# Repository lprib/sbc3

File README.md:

# sbc3: small computing environment
Self contained board that can be easily programmed on target for fun little
games or GUIs. Inspired by the environment presented by TI calculators and
TI-BASIC.

# Directory structure
```
sbc3
|_ art: various images for putting on PCB and for on-screen graphics
|_ cubemx: STM32 CubeMX projects for pinmapping
|_ docs: datasheets etc
|  |_ cpu_hardware: hardware support and layout for STM32s
|  |_ hardware: various datasheets for parts used
|  \_ sofware: CPU ref manuals etc
|_ img: images for docs
|_ keyboard_v1: kicad project for keyboard
|_ main_board_v1: kicad project for main board
|_ rust_firmware: Firmware and screen driver in Rust (abandoned for now)
\_ software: (mostly c++) software and firmware
   |_ cmake: cmake scripts
   |_ firmware: firmware for main_board_v1
   |  |_ app: main application sources
   |  \_ (other dirs): supporting libraries unchanged from CubeMX/FreeRTOS upstream
   \_ vm: virtual machine
      |_ analysis: jupyter notebook for vm stat calculations
      |_ engine: main vm sources (portable)
      |_ pc_port: raylib port of VM for desktop
      |_ programs: sbc3 assembly programs
      |_ tests: vm unit tests (lol)
      |_ vscode-extension-sbcs-syntax: syntax support in VSCode for SBC3 assembly
      \_ as2.py: sbc3 vm bytecode assembler
```

## Components
### main_board_v1
#### System diagram

#### PCB

#### Manufactured

- PCB and assembly done by JLCPCB
- Extended parts used:
  - TLV320DAC3101IRHBR Audio DAC
  - 475900001 Micro-USB connector
  - LD1117S33TR 3V3 Linear Regulator
    - Honestly can't remember why I went for this one instead of the JLC
    preferred part AMS1117-3.3. Maybe max current
  - LD1117S18TR 1V8 Linear Regulator (for DAC)
  - STM32F405VGT6 MCU

#### Changes and ideas for v2
- [ ] Ability to disconnect 3v3 from rs485 connectors
- [ ] Isolation transformers on rs485 for long connections
- [ ] External flash or eeprom or FRAM for filesystem
- [ ] "Cartridges" with flash
- [ ] Label all the headers pin for pin to avoid looking on the schematic every
time you're connecting the SWD
- [ ] Fix BOOT0/BOOT1? Or just 0ohm unpopulated for de-bricking?
- [ ] Proper enclosure
- [ ] ESD diode protection on all inputs
- [ ] External qspi flash (w25q128jv)
- [ ] Wire OE on LED shift registers to a PWMable pin! So you can easily pwm the brightness
- [ ] 18650 batteries + holder?
- [ ] smaller form factor with parts hidden underscreen and less rs485 or more
compact layout (look for resistor/cap sizing for 0402 wattage)
- [ ] ACTUALLY WIRE UP THE BUTTONS AND ENCODER THIS TIME!
    - Of all the things to screw up on the first PCB run, I didn't expect to
    completely forget to connect the button and rotary nets
- [ ] Tiny JST connectors really are shit! Hot pluggable trs circuit?
Enable/disabable power chip? Need to get this right before making a bunch of peripheral boards.

### keyboard_v1
#### System diagram

#### PCB

Not yet manufactured, since still thinking about re-doing the comms (definitely
not going to use the current JST connectors as theyre much too finicky).

### virtual machine
Also included is a stack based virtual bytecode machine (see [software/vm](./software/vm)).
The bytecode can call out to pre-defined system modules, including graphics
routines. Below is an example of the main board STM32 and a Linux desktop
running the same bytecode program.

#### STM32

#### Linux desktop

As the bytecode is stack based, a thin forth layer has been built for it, which
is currently assembled by a python script. See the source program for the above gifs [here](./software/vm/programs/tilemap.sbcs).

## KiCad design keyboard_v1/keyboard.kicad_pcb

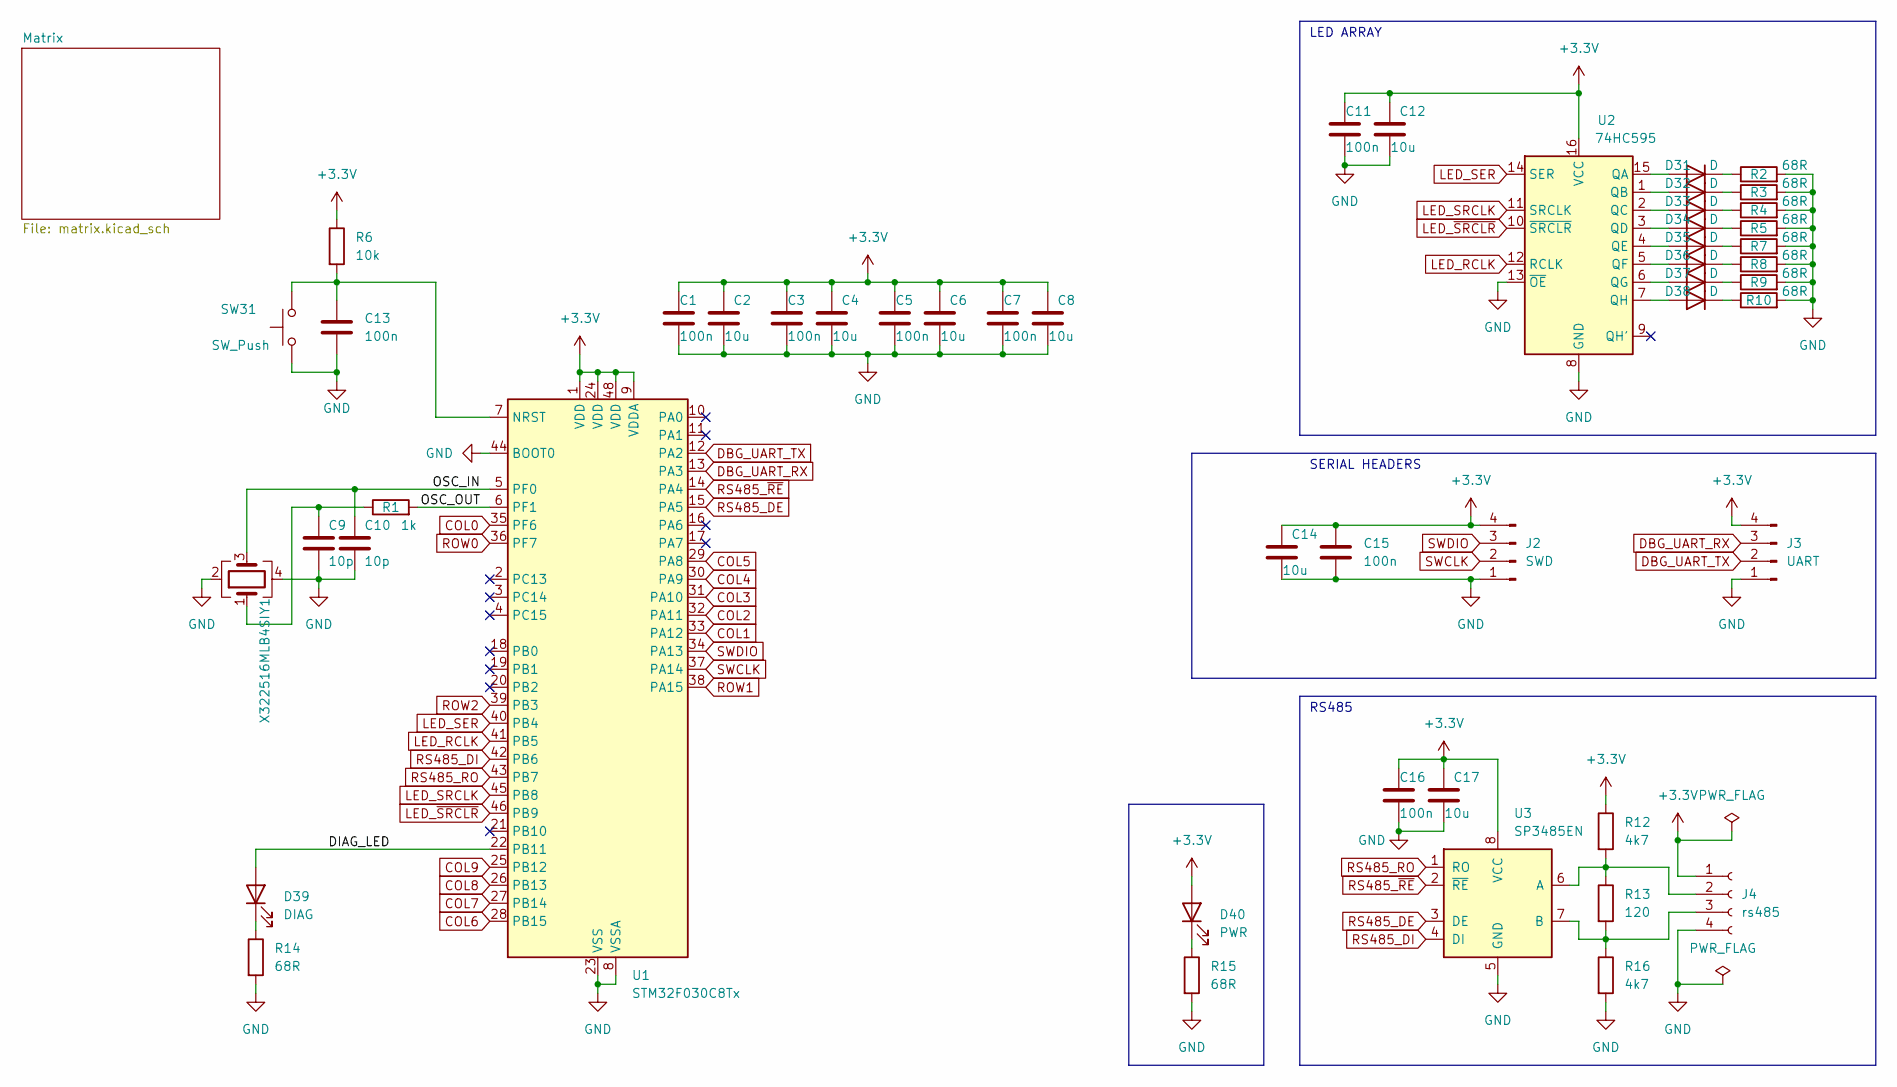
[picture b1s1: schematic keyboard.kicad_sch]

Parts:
C1, C3, C5, C7, C11, C13, C15, C16: 100n; C_0402_1005Metric; LCSC C307331
C2, C4, C6, C8, C12, C14, C17: 10u; C_0603_1608Metric; LCSC C96446
C9, C10: 10p; C_0402_1005Metric; LCSC C32949
D31, D32, D33, D34, D35, D36, D37, D38: D; D_0603_1608Metric; LCSC C72038
D39: DIAG; D_0603_1608Metric; LCSC C72038
D40: PWR; D_0603_1608Metric; LCSC C72038
J2: SWD; PinHeader_1x04_P2.54mm_Vertical
J3: UART; PinHeader_1x04_P2.54mm_Vertical
J4: rs485; JST_SH_SM04B-SRSS-TB_1x04-1MP_P1.00mm_Horizontal
R1: 1k; R_0402_1005Metric; LCSC C11702
R2, R3, R4, R5, R7, R8, R9, R10, R14, R15: 68R; R_0603_1608Metric; LCSC C27592
R6: 10k; R_0402_1005Metric; LCSC C25744
R12, R16: 4k7; R_1206_3216Metric; LCSC C17936
R13: 120; R_1206_3216Metric; LCSC C17909
SW31: SW_Push; SW_Push_1P1T_XKB_TS-1187A; LCSC C318884
U1: STM32F030C8Tx; LQFP-48_7x7mm_P0.5mm; LCSC C23922
U2: 74HC595; SOIC-16_3.9x9.9mm_P1.27mm; LCSC C5947
U3: SP3485EN; SOIC-8_3.9x4.9mm_P1.27mm
Y1: X322516MLB4SI; Crystal_SMD_SeikoEpson_TSX3225-4Pin_3.2x2.5mm; LCSC C13738

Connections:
+3.3V: C1.1, C2.1, C3.1, C4.1, C5.1, C6.1, C7.1, C8.1, C11.1, C12.1, C14.1, C15.1, C16.1, C17.1, D40.2 (A), J2.4, J3.4, J4.1, R6.1, R12.1, U1.1 (VDD), U1.9 (VDDA), U1.24 (VDD), U1.48 (VDD), U2.16 (VCC), U3.8 (VCC)
/DIAG_LED: D39.2 (A), U1.22 (PB11)
/OSC_IN: C10.1, U1.5 (PF0), Y1.3
/OSC_OUT: R1.2, U1.6 (PF1)
COL0: U1.35 (PF6); also elsewhere on the board
COL1: U1.33 (PA12); also elsewhere on the board
COL2: U1.32 (PA11); also elsewhere on the board
COL3: U1.31 (PA10); also elsewhere on the board
COL4: U1.30 (PA9); also elsewhere on the board
COL5: U1.29 (PA8); also elsewhere on the board
COL6: U1.28 (PB15); also elsewhere on the board
COL7: U1.27 (PB14); also elsewhere on the board
COL8: U1.26 (PB13); also elsewhere on the board
COL9: U1.25 (PB12); also elsewhere on the board
DBG_UART_RX: J3.3, U1.13 (PA3)
DBG_UART_TX: J3.2, U1.12 (PA2)
GND: C1.2, C2.2, C3.2, C4.2, C5.2, C6.2, C7.2, C8.2, C9.2, C10.2, C11.2, C12.2, C13.2, C14.2, C15.2, C16.2, C17.2, J2.1, J3.1, J4.4, R2.2, R3.2, R4.2, R5.2, R7.2, R8.2, R9.2, R10.2, R14.2, R15.2, R16.2, SW31.1, U1.8 (VSSA), U1.23 (VSS), U1.44 (BOOT0), U1.47 (VSS), U2.8 (GND), U2.13 (~OE), U3.5 (GND), Y1.2, Y1.4
LED_RCLK: U1.41 (PB5), U2.12 (RCLK)
LED_SER: U1.40 (PB4), U2.14 (SER)
LED_SRCLK: U1.45 (PB8), U2.11 (SRCLK)
LED_~SRCLR: U1.46 (PB9), U2.10 (~SRCLR)
unnamed: C9.1, R1.1, Y1.1
unnamed: D31.2 (A), U2.15 (QA)
unnamed: D31.1 (K), R2.1
unnamed: D32.2 (A), U2.1 (QB)
unnamed: D32.1 (K), R3.1
unnamed: D33.2 (A), U2.2 (QC)
unnamed: D33.1 (K), R4.1
unnamed: D34.2 (A), U2.3 (QD)
unnamed: D34.1 (K), R5.1
unnamed: D35.2 (A), U2.4 (QE)
unnamed: D35.1 (K), R7.1
unnamed: D36.2 (A), U2.5 (QF)
unnamed: D36.1 (K), R8.1
unnamed: D37.2 (A), U2.6 (QG)
unnamed: D37.1 (K), R9.1
unnamed: D38.2 (A), U2.7 (QH)
unnamed: D38.1 (K), R10.1
unnamed: D39.1 (K), R14.1
unnamed: D40.1 (K), R15.1
unnamed: J4.2, R12.2, R13.1, U3.6 (A)
unnamed: J4.3, R13.2, R16.1, U3.7 (B)
unnamed: C13.1, R6.2, SW31.2, U1.7 (NRST)
ROW0: U1.36 (PF7); also elsewhere on the board
ROW1: U1.38 (PA15); also elsewhere on the board
ROW2: U1.39 (PB3); also elsewhere on the board
RS485_DE: U1.15 (PA5), U3.3 (DE)
RS485_DI: U1.42 (PB6), U3.4 (DI)
RS485_RO: U1.43 (PB7), U3.1 (RO)
RS485_~RE: U1.14 (PA4), U3.2 (~RE)
SWCLK: J2.2, U1.37 (PA14)
SWDIO: J2.3, U1.34 (PA13)

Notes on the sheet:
RS485
SERIAL HEADERS
LED ARRAY

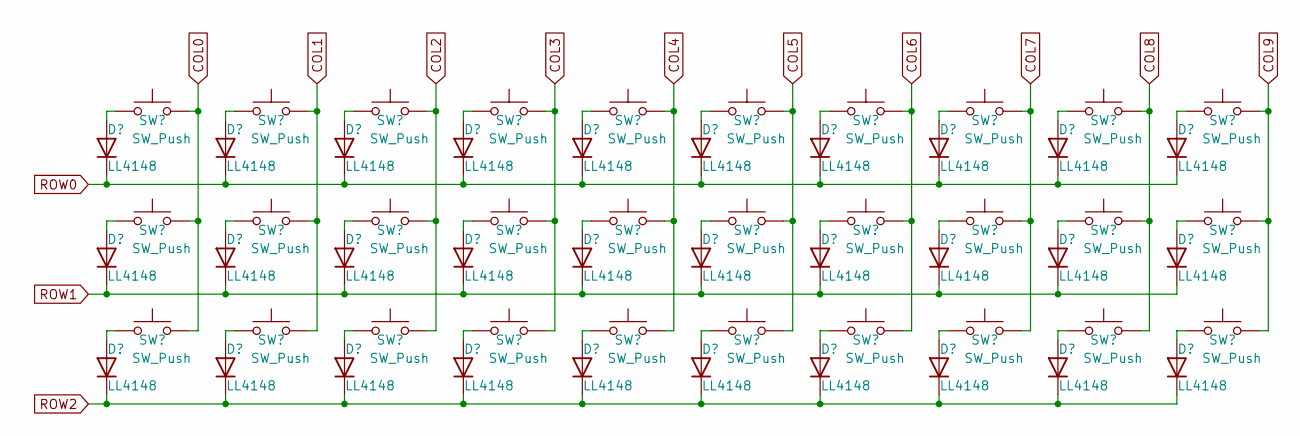
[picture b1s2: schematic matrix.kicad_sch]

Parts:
D1, D2, D3, D4, D5, D6, D7, D8, D9, D10, D11, D12, D13, D14, D15, D16, D17, D18, D19, D20, D21, D22, D23, D24, D25, D26, D27, D28, D29, D30: LL4148; D_1206_3216Metric; LCSC C9808
SW1, SW2, SW3, SW4, SW5, SW6, SW7, SW8, SW9, SW10, SW11, SW12, SW13, SW14, SW15, SW16, SW17, SW18, SW19, SW20, SW21, SW22, SW23, SW24, SW25, SW26, SW27, SW28, SW29, SW30: SW_Push; SW_Cherry_MX_1.00u_PCB

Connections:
COL0: SW1.2, SW11.2, SW21.2; also elsewhere on the board
COL1: SW2.2, SW12.2, SW22.2; also elsewhere on the board
COL2: SW3.2, SW13.2, SW23.2; also elsewhere on the board
COL3: SW4.2, SW14.2, SW24.2; also elsewhere on the board
COL4: SW5.2, SW15.2, SW25.2; also elsewhere on the board
COL5: SW6.2, SW16.2, SW26.2; also elsewhere on the board
COL6: SW7.2, SW17.2, SW27.2; also elsewhere on the board
COL7: SW8.2, SW18.2, SW28.2; also elsewhere on the board
COL8: SW9.2, SW19.2, SW29.2; also elsewhere on the board
COL9: SW10.2, SW20.2, SW30.2; also elsewhere on the board
unnamed: D1.2 (A), SW1.1
unnamed: D2.2 (A), SW2.1
unnamed: D3.2 (A), SW3.1
unnamed: D4.2 (A), SW4.1
unnamed: D5.2 (A), SW5.1
unnamed: D6.2 (A), SW6.1
unnamed: D7.2 (A), SW7.1
unnamed: D8.2 (A), SW8.1
unnamed: D9.2 (A), SW9.1
unnamed: D10.2 (A), SW10.1
unnamed: D11.2 (A), SW11.1
unnamed: D12.2 (A), SW12.1
unnamed: D13.2 (A), SW13.1
unnamed: D14.2 (A), SW14.1
unnamed: D15.2 (A), SW15.1
unnamed: D16.2 (A), SW16.1
unnamed: D17.2 (A), SW17.1
unnamed: D18.2 (A), SW18.1
unnamed: D19.2 (A), SW19.1
unnamed: D20.2 (A), SW20.1
unnamed: D21.2 (A), SW21.1
unnamed: D22.2 (A), SW22.1
unnamed: D23.2 (A), SW23.1
unnamed: D24.2 (A), SW24.1
unnamed: D25.2 (A), SW25.1
unnamed: D26.2 (A), SW26.1
unnamed: D27.2 (A), SW27.1
unnamed: D28.2 (A), SW28.1
unnamed: D29.2 (A), SW29.1
unnamed: D30.2 (A), SW30.1
ROW0: D1.1 (K), D2.1 (K), D3.1 (K), D4.1 (K), D5.1 (K), D6.1 (K), D7.1 (K), D8.1 (K), D9.1 (K), D10.1 (K); also elsewhere on the board
ROW1: D11.1 (K), D12.1 (K), D13.1 (K), D14.1 (K), D15.1 (K), D16.1 (K), D17.1 (K), D18.1 (K), D19.1 (K), D20.1 (K); also elsewhere on the board
ROW2: D21.1 (K), D22.1 (K), D23.1 (K), D24.1 (K), D25.1 (K), D26.1 (K), D27.1 (K), D28.1 (K), D29.1 (K), D30.1 (K); also elsewhere on the board

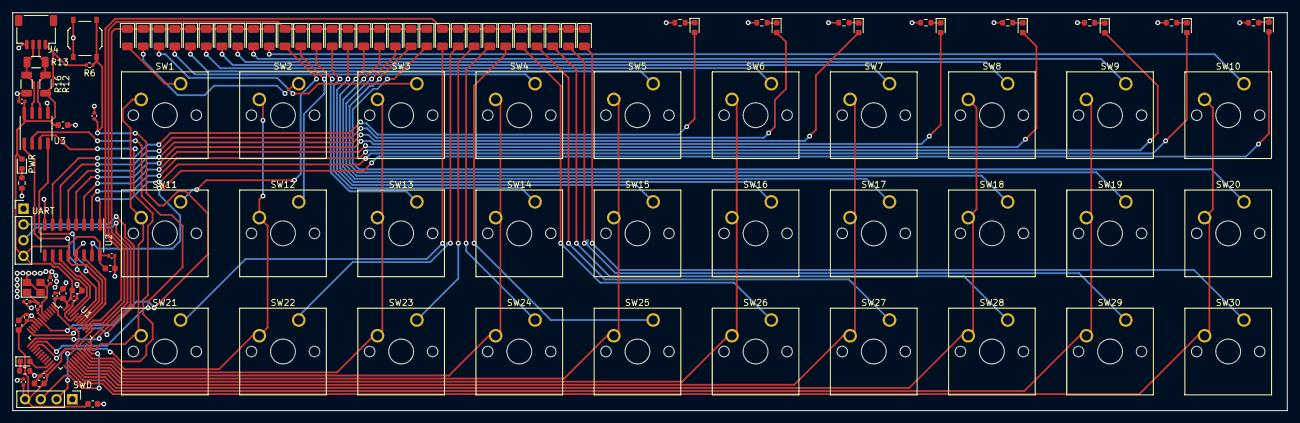
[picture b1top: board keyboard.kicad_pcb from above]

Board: 2 copper layers, 205.5 x 64.2 mm, 110 parts (0 on the bottom side), 82 nets.

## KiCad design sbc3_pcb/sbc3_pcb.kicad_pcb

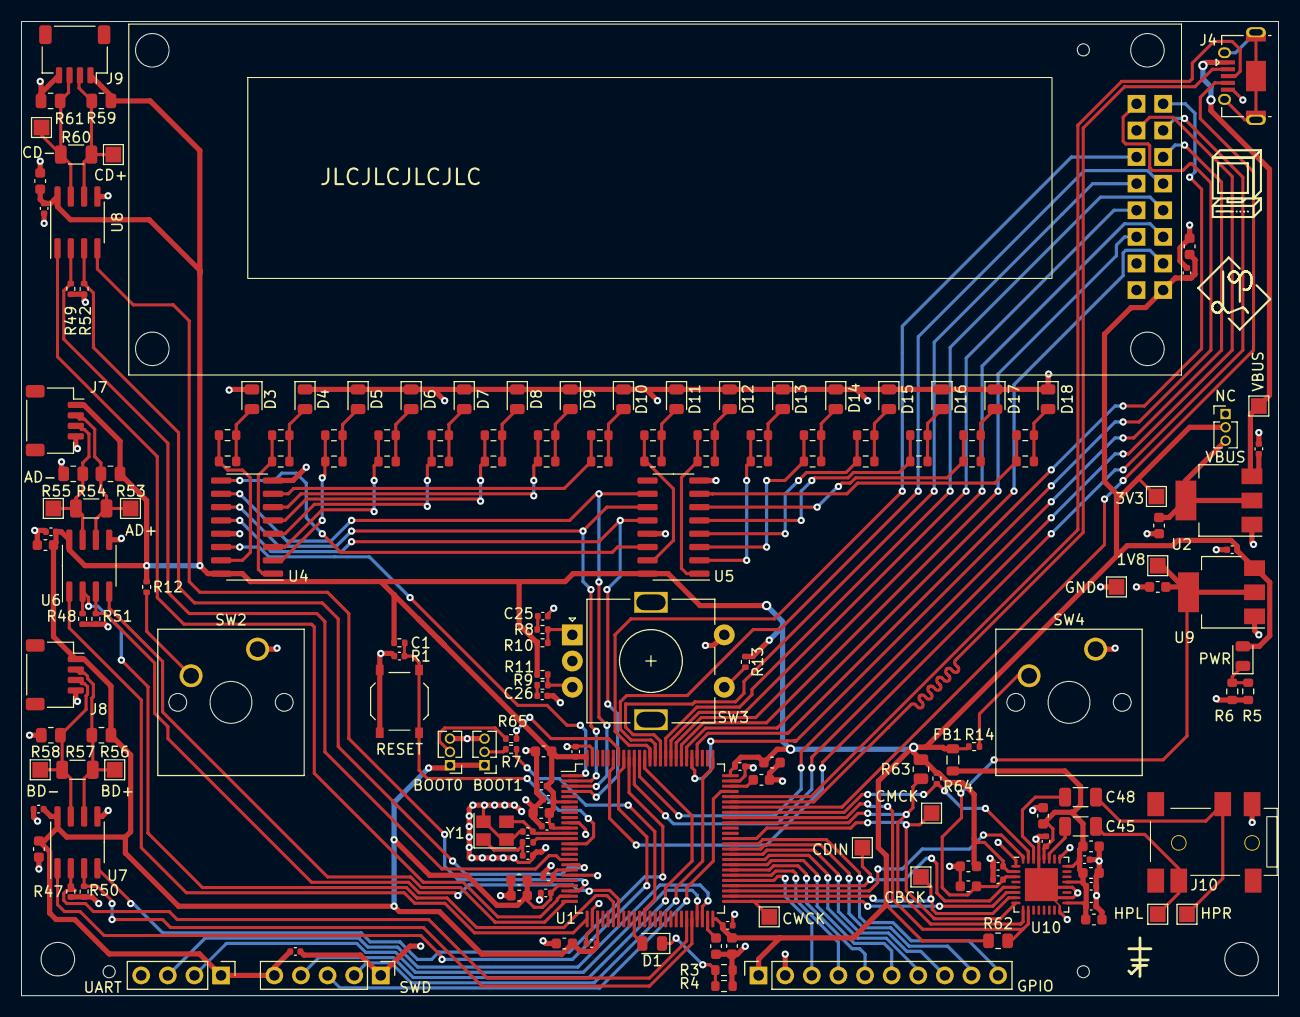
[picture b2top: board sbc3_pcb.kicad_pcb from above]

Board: 2 copper layers, 120.0 x 93.0 mm, 181 parts (0 on the bottom side), 122 nets.

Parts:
C1, C6, C9, C11, C12, C14, C17, C18, C20, C22, C24, C28, C29, C31, C33, C35, C40, C42, C44, C47, C50, C52: 100n; C_0402_1005Metric
C2, C3: 10p; C_0402_1005Metric
C4, C5: 2.2u; C_0603_1608Metric
C7: 1u; C_0402_1005Metric
C8, C10, C13, C15, C16, C19, C21, C23, C27, C30, C32, C34, C36, C39, C41, C43, C46, C49, C51: 10u; C_0603_1608Metric
C25, C26: 10n; C_0402_1005Metric
C45, C48: 47u; C_1206_3216Metric
D1: DBG; LED_0805_2012Metric
D2: PWR; LED_0805_2012Metric
D3, D4, D5, D6, D7, D8, D9, D10, D11, D12, D13, D14, D15, D16, D17, D18: LED; LED_0805_2012Metric
FB1: FerriteBead; L_0805_2012Metric
H1, H2: MountingHole; MountingHole_3.2mm_M3
H3, H4, H5: MountingHole; MountingHole_JLCPCB_Assembly
J1: VBUS CON; PinHeader_1x03_P1.27mm_Vertical
J2: BOOT0; PinHeader_1x03_P1.27mm_Vertical
J3: GPIO; PinSocket_1x10_P2.54mm_Vertical
J4: USB_B_Micro; USB_Micro-AB_Molex_47590-0001
J5: UART; PinHeader_1x04_P2.54mm_Vertical
J6: SWD; PinHeader_1x05_P2.54mm_Vertical
J7, J8, J9: Conn_01x04_Socket; JST_SH_SM04B-SRSS-TB_1x04-1MP_P1.00mm_Horizontal
J10: PJ-342
J11: BOOT1; PinHeader_1x03_P1.27mm_Vertical
R1, R7, R8, R9, R10, R11, R12, R13, R14, R47, R48, R49, R50, R51, R52, R64, R65: 10k; R_0402_1005Metric
R2: 1k; R_0402_1005Metric
R3, R4, R5, R6, R15, R16, R17, R18, R19, R20, R21, R22, R23, R24, R25, R26, R27, R28, R29, R30, R31, R32, R33, R34, R35, R36, R37, R38, R39, R40, R41, R42, R43, R44, R45, R46: 150; R_0603_1608Metric
R53, R55, R56, R58, R59, R61, R62, R63: 4k7; R_0805_2012Metric
R54, R57, R60: 120; R_1206_3216Metric
SW1: RESET; SW_Push_1P1T_XKB_TS-1187A
SW2, SW4: CHERRY_SWITCH; SW_Cherry_MX_1.00u_PCB
SW3: RotaryEncoder_Switch; RotaryEncoder_Alps_EC11E-Switch_Vertical_H20mm
TP1: 3V3; MyTP
TP3: VBUS; MyTP
TP4: AD+; MyTP
TP5: AD-; MyTP
TP6: BD+; MyTP
TP7: BD-; MyTP
TP8: CD+; MyTP
TP9: CD-; MyTP
TP10: 1V8; MyTP
TP11: CMCK; MyTP
TP12: CDIN; MyTP
TP13: CBCK; MyTP
TP14: CWCK; MyTP
TP15: HPR; MyTP
TP16: HPL; MyTP
TP17: GND; MyTP
U1: STM32F405VGT6; LQFP-100_14x14mm_P0.5mm
U2: LD1117S33TR_SOT223; SOT-223-3_TabPin2
U3: 256x64 SSD1322 Module; SSD1322_oled_module_3.12inch
U4, U5: 74HC595D,118; SOIC-16_3.9x9.9mm_P1.27mm
U6, U7, U8: SP3485EN-L/TR; SOIC-8_3.9x4.9mm_P1.27mm
U9: LD1117S18TR_SOT223; SOT-223-3_TabPin2
U10: TLV320DAC3101IRHBR; VQFN-32-1EP_5x5mm_P0.5mm_EP3.15x3.15mm
Y1: 16MHz; Crystal_SMD_3225-4Pin_3.2x2.5mm

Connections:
+1V8: C36.1, C51.1, C52.1, TP10.1, U9.2 (VO), U10.3 (DVDD)
+3.3V: C6.1, C7.1, C8.1, C9.1, C10.1, C12.1, C13.1, C14.1, C15.1, C17.1, C18.1, C19.1, C20.1, C21.1, C22.1, C23.1, C24.1, C27.1, C28.1, C29.1, C30.1, C31.1, C32.1, C33.1, C34.1, C35.1, C49.1, C50.1, D2.2 (A), FB1.1, J1.2, J2.1, J3.1, J5.1, J6.5, J7.1, J8.1, J9.1, J11.1, R1.2, R10.2, R11.2, R12.1, R13.1, R14.1, R53.1, R56.1, R59.1, R62.1, R63.1, R64.1, TP1.1, U1.6 (VBAT), U1.11 (VDD), U1.19 (VDD), U1.21 (VREF+), U1.22 (VDDA), U1.28 (VDD), U1.50 (VDD), U1.75 (VDD), U1.100 (VDD), U3.2 (VCC), U4.16 (VCC), U5.16 (VCC), U6.8 (VCC), U7.8 (VCC), U8.8 (VCC), U9.3 (VI), U10.2 (IOVDD)
/Audio/HPL_OUT: C45.1, J10.5 (T), TP16.1
/Audio/HPL_PRE: C45.2, U10.27 (HPL)
/Audio/HPR_OUT: C48.1, J10.4 (R2), TP15.1
/Audio/HPR_PRE: C48.2, U10.30 (HPR)
/Audio/HP_VDD: C39.1, C40.1, C41.1, C42.1, C43.1, C44.1, C46.1, C47.1, FB1.2, U10.17 (AVDD), U10.21 (SPLVDD), U10.24 (SPRVDD), U10.28 (HPVDD)
/BOOT0: R7.2, U1.94 (BOOT0)
/BOOT1: R65.2, U1.37 (PB2)
/CODEC_BCLK: TP13.1, U1.52 (PB13), U10.7 (BCLK)
/CODEC_DIN: TP12.1, U1.54 (PB15), U10.5 (DIN)
/CODEC_GPIO1: U1.53 (PB14), U10.32 (GPIO1)
/CODEC_MCLK: TP11.1, U1.63 (PC6), U10.8 (MCLK)
/CODEC_NRESET: R64.2, U1.68 (PA9), U10.31 (~RESET)
/CODEC_SCL: R62.2, U1.67 (PA8), U10.10 (SCL)
/CODEC_SDA: R63.2, U1.66 (PC9), U10.9 (SDA)
/CODEC_WCLK: TP14.1, U1.51 (PB12), U10.6 (WCLK)
/Comms/RS485_A_D+: J7.2, R53.2, R54.1, TP4.1, U6.6 (A)
/Comms/RS485_A_D-: J7.3, R54.2, R55.1, TP5.1, U6.7 (B)
/Comms/RS485_B_D+: J8.2, R56.2, R57.1, TP6.1, U7.6 (A)
/Comms/RS485_B_D-: J8.3, R57.2, R58.1, TP7.1, U7.7 (B)
/Comms/RS485_C_D+: J9.2, R59.2, R60.1, TP8.1, U8.6 (A)
/Comms/RS485_C_D-: J9.3, R60.2, R61.1, TP9.1, U8.7 (B)
/DBG_LED: D1.2 (A), U1.35 (PB0)
/DBG_UART_RX: J5.3, U1.48 (PB11)
/DBG_UART_TX: J5.2, U1.47 (PB10)
/EXT_A.DE: R51.1, U1.32 (PA7), U6.3 (DE)
/EXT_A.DI: U1.25 (PA2), U6.4 (DI)
/EXT_A.NRE: R48.1, U1.31 (PA6), U6.2 (~RE)
/EXT_A.RO: U1.26 (PA3), U6.1 (RO)
/EXT_B.DE: R50.1, U1.46 (PE15), U7.3 (DE)
/EXT_B.DI: U1.92 (PB6), U7.4 (DI)
/EXT_B.NRE: R47.1, U1.45 (PE14), U7.2 (~RE)
/EXT_B.RO: U1.93 (PB7), U7.1 (RO)
/EXT_C.DE: R52.1, U1.18 (PC3), U8.3 (DE)
/EXT_C.DI: U1.23 (PA0), U8.4 (DI)
/EXT_C.NRE: R49.1, U1.17 (PC2), U8.2 (~RE)
/EXT_C.RO: U1.24 (PA1), U8.1 (RO)
/GPIOA_0: J3.3, U1.55 (PD8)
/GPIOA_1: J3.4, U1.56 (PD9)
/GPIOA_2: J3.5, U1.57 (PD10)
/GPIOA_3: J3.6, U1.58 (PD11)
/GPIOA_4: J3.7, U1.59 (PD12)
/GPIOA_5: J3.8, U1.60 (PD13)
/GPIOA_6: J3.9, U1.61 (PD14)
/GPIOA_7: J3.10, U1.62 (PD15)
/LEDS.RCLK: U1.4 (PE5), U4.12 (RCLK), U5.12 (RCLK)
/LEDS.SER: U1.1 (PE2), U4.14 (SER)
/LEDS.SRCLK: U1.2 (PE3), U4.11 (SRCLK), U5.11 (SRCLK)
/LEDS.SRCLR: U1.3 (PE4), U4.10 (~SRCLR), U5.10 (~SRCLR)
/MMI_ROTARY_A: C26.1, R9.1
/MMI_ROTARY_B: C25.1, R8.1
/MMI_ROTARY_PUSH: R13.2, SW3.S1
/MMI_SW_A: R12.2, SW2.2
/MMI_SW_B: R14.2, SW4.2
/OSC_IN: C3.1, U1.12 (PH0), Y1.3
/OSC_OUT: R2.2, U1.13 (PH1)
/SCR.CS: U1.79 (PC11), U3.16 (~CS)
/SCR.D0: U1.81 (PD0), U3.4 (D0/SCLK)
/SCR.D1: U1.82 (PD1), U3.5 (D1/SDATA)
/SCR.D2: U1.83 (PD2), U3.6 (D2)
/SCR.D3: U1.84 (PD3), U3.7 (D3)
/SCR.D4: U1.85 (PD4), U3.8 (D4)
/SCR.D5: U1.86 (PD5), U3.9 (D5)
/SCR.D6: U1.87 (PD6), U3.10 (D6)
/SCR.D7: U1.88 (PD7), U3.11 (D7)
/SCR.DC: U1.95 (PB8), U3.14 (D~C)
/SCR.E: U1.90 (PB4), U3.12 (E/~RD)
/SCR.RST: U1.80 (PC12), U3.15 (~RST)
/SCR.RW: U1.91 (PB5), U3.13 (R~W)
/SWD_CLK: J6.2, U1.76 (PA14)
/SWD_IO: J6.3, U1.72 (PA13)
/SWD_O: J6.4, U1.89 (PB3)
/USB_D+: J4.3 (D+), U1.71 (PA12)
/USB_D-: J4.2 (D-), U1.70 (PA11)
/USB_ID: J4.4 (ID), U1.69 (PA10)
/USB_VBUS: C11.1, J4.1 (VBUS), TP3.1, U2.3 (VI)
GND: C1.2, C2.2, C3.2, C4.2, C5.2, C6.2, C7.2, C8.2, C9.2, C10.2, C11.2, C12.2, C13.2, C14.2, C15.2, C16.2, C17.2, C18.2, C19.2, C20.2, C21.2, C22.2, C23.2, C24.2, C25.2, C26.2, C27.2, C28.2, C29.2, C30.2, C31.2, C32.2, C33.2, C34.2, C35.2, C36.2, C39.2, C40.2, C41.2, C42.2, C43.2, C44.2, C46.2, C47.2, C49.2, C50.2, C51.2, C52.2, D3.1 (K), D4.1 (K), D5.1 (K), D6.1 (K), D7.1 (K), D8.1 (K), D9.1 (K), D10.1 (K), D11.1 (K), D12.1 (K), D13.1 (K), D14.1 (K), D15.1 (K), D16.1 (K), D17.1 (K), D18.1 (K), J2.3, J3.2, J4.5 (GND), J5.4, J6.1, J7.4, J8.4, J9.4, J10.2 (S), J11.3, R3.2, R4.2, R5.2, R6.2, R47.2, R48.2, R49.2, R50.2, R51.2, R52.2, R55.2, R58.2, R61.2, SW1.1, SW2.1, SW3.C, SW3.S2, SW4.1, TP17.1, U1.10 (VSS), U1.20 (VSSA), U1.27 (VSS), U1.74 (VSS), U1.99 (VSS), U2.1 (GND), U3.1 (VSS), U4.8 (GND), U4.13 (~OE), U5.8 (GND), U5.13 (~OE), U6.5 (GND), U7.5 (GND), U8.5 (GND), U9.1 (GND), U10.1 (IOVSS), U10.16 (AVSS), U10.18 (DVSS), U10.20 (SPLVSS), U10.25 (SPRVSS), U10.29 (HPVSS), U10.33 (PAD), Y1.2, Y1.4
unnamed: C2.1, R2.1, Y1.1
unnamed: D1.1 (K), R3.1, R4.1
unnamed: D2.1 (K), R5.1, R6.1
unnamed: D3.2 (A), R15.2, R16.2
unnamed: D4.2 (A), R17.2, R18.2
unnamed: D5.2 (A), R19.2, R20.2
unnamed: D6.2 (A), R21.2, R22.2
unnamed: D7.2 (A), R23.2, R24.2
unnamed: D8.2 (A), R25.2, R26.2
unnamed: D9.2 (A), R27.2, R28.2
unnamed: D10.2 (A), R29.2, R30.2
unnamed: D11.2 (A), R31.2, R32.2
unnamed: D12.2 (A), R33.2, R34.2
unnamed: D13.2 (A), R35.2, R36.2
unnamed: D14.2 (A), R37.2, R38.2
unnamed: D15.2 (A), R39.2, R40.2
unnamed: D16.2 (A), R41.2, R42.2
unnamed: D17.2 (A), R43.2, R44.2
unnamed: D18.2 (A), R45.2, R46.2
unnamed: C16.1, J1.3, U2.2 (VO)
unnamed: J2.2, R7.1
unnamed: J11.2, R65.1
unnamed: R8.2, R10.1, SW3.A
unnamed: R9.2, R11.1, SW3.B
unnamed: C1.1, R1.1, SW1.2, U1.14 (NRST)
unnamed: C4.1, U1.49 (VCAP_1)
unnamed: C5.1, U1.73 (VCAP_2)
unnamed: R15.1, R16.1, U4.15 (QA)
unnamed: R17.1, R18.1, U4.1 (QB)
unnamed: R19.1, R20.1, U4.2 (QC)
unnamed: R21.1, R22.1, U4.3 (QD)
unnamed: R23.1, R24.1, U4.4 (QE)
unnamed: R25.1, R26.1, U4.5 (QF)
unnamed: R27.1, R28.1, U4.6 (QG)
unnamed: U4.9 (QH'), U5.14 (SER)
unnamed: R29.1, R30.1, U4.7 (QH)
unnamed: R31.1, R32.1, U5.15 (QA)
unnamed: R33.1, R34.1, U5.1 (QB)
unnamed: R35.1, R36.1, U5.2 (QC)
unnamed: R37.1, R38.1, U5.3 (QD)
unnamed: R39.1, R40.1, U5.4 (QE)
unnamed: R41.1, R42.1, U5.5 (QF)
unnamed: R43.1, R44.1, U5.6 (QG)
unnamed: R45.1, R46.1, U5.7 (QH)

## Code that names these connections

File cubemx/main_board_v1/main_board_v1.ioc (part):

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Mcu.Name=STM32F405VGTx
Mcu.Package=LQFP100
Mcu.UserName=STM32F405VGTx
PA0-WKUP.Mode=Asynchronous
PA0-WKUP.Signal=UART4_TX
PA1.Mode=Asynchronous
PA1.Signal=UART4_RX
PA10.Mode=OTG/Dual_Role_Device
PA10.Signal=USB_OTG_FS_ID
PA11.Mode=OTG/Dual_Role_Device
PA11.Signal=USB_OTG_FS_DM
PA12.Mode=OTG/Dual_Role_Device
PA12.Signal=USB_OTG_FS_DP
PA13.Mode=Trace_Asynchronous_SW
PA13.Signal=SYS_JTMS-SWDIO
PA14.Mode=Trace_Asynchronous_SW
PA14.Signal=SYS_JTCK-SWCLK
PA2.Mode=Asynchronous
PA2.Signal=USART2_TX
PA3.Mode=Asynchronous
PA3.Signal=USART2_RX
PA4.Signal=COMP_DAC1_group
PA5.Signal=COMP_DAC2_group
PA6.Signal=GPIO_Output
PA7.Signal=GPIO_Output
PA8.Mode=I2C
PA8.Signal=I2C3_SCL
PA9.GPIOParameters=GPIO_Label
PA9.GPIO_Label=CODEC_NRESET
PA9.Signal=GPIO_Output
PB0.GPIOParameters=GPIO_Label
PB0.GPIO_Label=DBG_LED
PB0.Signal=GPIO_Output
PB10.Mode=Asynchronous
PB10.Signal=USART3_TX
PB11.Mode=Asynchronous
PB11.Signal=USART3_RX
PB12.Mode=Half_Duplex_Master
PB12.Signal=I2S2_WS
PB13.Mode=Half_Duplex_Master
PB13.Signal=I2S2_CK
PB14.GPIOParameters=GPIO_Label
PB14.GPIO_Label=CODEC_GPIO1
PB14.Signal=GPIO_Input
PB15.Mode=Half_Duplex_Master
PB15.Signal=I2S2_SD
PB2.GPIOParameters=GPIO_Label
PB2.GPIO_Label=BOOT1
PB2.Signal=GPIO_Input
PB3.Mode=Trace_Asynchronous_SW
PB3.Signal=SYS_JTDO-SWO
PB4.Signal=GPIO_Output
PB5.Signal=GPIO_Output
PB6.Mode=Asynchronous
PB6.Signal=USART1_TX
PB7.Mode=Asynchronous
PB7.Signal=USART1_RX
PB8.Signal=GPIO_Output
PC11.Signal=GPIO_Output
PC12.Signal=GPIO_Output
PC2.Signal=GPIO_Output
PC3.Signal=GPIO_Output
PC6.Mode=Master_Clock_Activated
PC6.Signal=I2S2_MCK
PC9.Mode=I2C
PC9.Signal=I2C3_SDA
PD0.Signal=GPIO_Output
PD1.Signal=GPIO_Output
PD2.Signal=GPIO_Output
PD3.Signal=GPIO_Output
PD4.Signal=GPIO_Output
PD5.Signal=GPIO_Output
PD6.Signal=GPIO_Output
PD7.Signal=GPIO_Output
PE14.Signal=GPIO_Output
PE15.Signal=GPIO_Analog
PE2.Signal=GPIO_Output
PE3.Signal=GPIO_Output
PE4.Signal=GPIO_Output
PE5.Signal=GPIO_Output
PH0-OSC_IN.Mode=HSE-External-Oscillator
PH0-OSC_IN.Signal=RCC_OSC_IN
PH1-OSC_OUT.Mode=HSE-External-Oscillator
PH1-OSC_OUT.Signal=RCC_OSC_OUT
RCC.HSE_VALUE=16000000
RCC.SYSCLKFreq_VALUE=168000000
RCC.SYSCLKSource=RCC_SYSCLKSOURCE_PLLCLK
board=custom

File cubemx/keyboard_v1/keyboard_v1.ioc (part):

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Mcu.Name=STM32F030C8Tx
Mcu.Package=LQFP48
Mcu.UserName=STM32F030C8Tx
PA10.Signal=GPIO_Output
PA11.Signal=GPIO_Output
PA12.Signal=GPIO_Output
PA13.Mode=Serial_Wire
PA13.Signal=SYS_SWDIO
PA14.Mode=Serial_Wire
PA14.Signal=SYS_SWCLK
PA15.Signal=GPIO_Input
PA2.Mode=Asynchronous
PA2.Signal=USART2_TX
PA3.Mode=Asynchronous
PA3.Signal=USART2_RX
PA4.Signal=GPIO_Output
PA5.Signal=GPIO_Output
PA8.Signal=GPIO_Output
PA9.Signal=GPIO_Output
PB12.Signal=GPIO_Output
PB13.Signal=GPIO_Output
PB14.Signal=GPIO_Output
PB15.Signal=GPIO_Output
PB3.Signal=GPIO_Input
PB4.Signal=GPIO_Output
PB5.Signal=GPIO_Output
PB6.Mode=Asynchronous
PB6.Signal=USART1_TX
PB7.Mode=Asynchronous
PB7.Signal=USART1_RX
PB8.Signal=GPIO_Output
PB9.Signal=GPIO_Output
PF0-OSC_IN.Mode=HSE-External-Oscillator
PF0-OSC_IN.Signal=RCC_OSC_IN
PF1-OSC_OUT.Mode=HSE-External-Oscillator
PF1-OSC_OUT.Signal=RCC_OSC_OUT
PF6.Signal=GPIO_Output
PF7.Signal=GPIO_Input
board=custom

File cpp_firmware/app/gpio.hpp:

#pragma once

#include <stdint.h>

#include "stm32f405xx.h"
#include "stm32f4xx_ll_gpio.h"

namespace gpio {

void init();

class pin_t {
public:
   constexpr pin_t(GPIO_TypeDef* _port, uint16_t _pin) :
      port(_port),
      pin(_pin) {}

   void to_lowspeed_pp_out() const {
      configure(
         LL_GPIO_MODE_OUTPUT,
         LL_GPIO_OUTPUT_PUSHPULL,
         LL_GPIO_PULL_NO,
         LL_GPIO_SPEED_FREQ_LOW,
         LL_GPIO_AF_0
      );
   }

   void to_highspeed_pp_out() const {
      configure(
         LL_GPIO_MODE_OUTPUT,
         LL_GPIO_OUTPUT_PUSHPULL,
         LL_GPIO_PULL_NO,
         LL_GPIO_SPEED_FREQ_VERY_HIGH,
         LL_GPIO_AF_0
      );
   }

   void to_lowspeed_in() const {
      configure(
         LL_GPIO_MODE_INPUT,
         LL_GPIO_OUTPUT_PUSHPULL,
         LL_GPIO_PULL_NO,
         LL_GPIO_SPEED_FREQ_LOW,
         LL_GPIO_AF_0
      );
   }

   void use_alternate_function(uint8_t alternate_function) const {
      configure(
         LL_GPIO_MODE_ALTERNATE,
         LL_GPIO_OUTPUT_PUSHPULL,
         LL_GPIO_PULL_NO,
         LL_GPIO_SPEED_FREQ_VERY_HIGH,
         static_cast<uint32_t>(alternate_function)
      );
   }

   void write(bool value) const {
      if(value) {
         LL_GPIO_SetOutputPin(port, pin);
      } else {
         LL_GPIO_ResetOutputPin(port, pin);
      }
   }

   void toggle() const {
      LL_GPIO_TogglePin(port, pin);
   }

   bool read() const {
      return LL_GPIO_IsInputPinSet(port, pin);
   }

private:
   GPIO_TypeDef* const port;
   uint16_t const pin;

   void configure(
      uint32_t mode, uint32_t otype, uint32_t pull, uint32_t speed, uint32_t alt
   ) const {
      LL_GPIO_SetPinMode(port, pin, mode);
      LL_GPIO_SetPinOutputType(port, pin, otype);
      LL_GPIO_SetPinSpeed(port, pin, speed);
      LL_GPIO_SetPinPull(port, pin, pull);
      if(pin & 0xff) {
         LL_GPIO_SetAFPin_0_7(port, pin, alt);
      } else {
         LL_GPIO_SetAFPin_8_15(port, pin, alt);
      }
   }
};

const pin_t dbg_led{GPIOB, LL_GPIO_PIN_0};
const pin_t led_ser{GPIOE, LL_GPIO_PIN_2};
const pin_t led_srclk{GPIOE, LL_GPIO_PIN_3};
const pin_t led_srclr{GPIOE, LL_GPIO_PIN_4};
const pin_t led_rclk{GPIOE, LL_GPIO_PIN_5};
const pin_t gp0{GPIOD, LL_GPIO_PIN_8};
const pin_t gp1{GPIOD, LL_GPIO_PIN_9};
const pin_t gp2{GPIOD, LL_GPIO_PIN_10};
const pin_t gp3{GPIOD, LL_GPIO_PIN_11};
const pin_t gp4{GPIOD, LL_GPIO_PIN_12};
const pin_t gp5{GPIOD, LL_GPIO_PIN_13};
const pin_t gp6{GPIOD, LL_GPIO_PIN_14};
const pin_t gp7{GPIOD, LL_GPIO_PIN_15};

const pin_t scr_e{GPIOB, LL_GPIO_PIN_4};
const pin_t scr_rw{GPIOB, LL_GPIO_PIN_5};
const pin_t scr_dc{GPIOB, LL_GPIO_PIN_8};
const pin_t scr_cs{GPIOC, LL_GPIO_PIN_11};
const pin_t scr_res{GPIOC, LL_GPIO_PIN_12};

} // namespace gpio

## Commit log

2023-11-17 Keyboard schematic, file restructure
2023-11-17 dont commit lock files
2023-11-18 Initial runup with STM32CubeMX
2023-11-18 remove boot selector on keyboard
2023-11-19 finally, a rust blinky
2023-11-19 VsCode cortex-debug working
2023-11-19 move main schematic
2023-11-20 C UART test
2023-11-20 integrate ledstrip library, uart
2023-11-20 keyboard PCB updates
2023-11-20 Failed attempt at IoPin (interface will be removed in embedded_hal 1.0 anyway :/ )
2023-11-22 reorganize, try to get display working
2023-11-22 swapped data/command
2023-11-22 write command and write data working
2023-11-22 finally works!
2023-11-23 broke screen again, println!
2023-11-23 Fix some small bugs in screen driver
2023-11-23 More specific trait name
2023-11-27 Some restructures, get libui basics going
2023-11-27 greyscale test
2023-12-02 PC emulator of screen
2023-12-03 specify font format, add font compiler
2023-12-03 distinguishable bg color for pc pixels
2023-12-03 working bitap font rendering
2023-12-16 test symbols
2024-01-14 firmware -> rust_firmware
2024-01-21 Make CMake project build (yet untested)
2024-01-21 stm corex m4 programming manual
2024-01-21 phony targets
2024-01-22 -Os hardcoded for now
2024-01-22 toy example working after much pain
2024-01-22 cosmetic change
2024-01-22 simplify hal linking
2024-01-22 FreeRTOS working!
2024-01-24 simplify cmake, c++ify some things
2024-01-24 add warnings and fix them
2024-01-24 gpio
2024-01-25 animation
2024-01-25 cortex-debug working (it's that easy...)
2024-01-25 prematurely optimize gpios
2024-01-25 jank ass ledstrip
2024-01-29 delay us but multiple labels
2024-01-29 coretx docs
2024-02-02 last commit before laptop nuke
2024-02-04 remove `--specs=nosys.specs` because it angers the linker...?
2024-02-04 makefile -> script
2024-02-04 "fix" RWX section error
2024-02-04 new delay us, leds ting
2024-02-04 add armv7 arch manual
2024-02-04 add uart that doesnt work :^)
2024-02-04 add debug profile and reorg gitignore
2024-02-04 Fix uart (forgot alternate function :^))
2024-02-04 add hal docs
2024-02-04 Organize docs
2024-02-05 hardcode uarts
2024-02-05 Low-level uart transmit driver, after much pain
2024-02-06 fix intellisense
2024-02-06 nice serial API (for usart3 only :^))
2024-02-06 better error, mutex with lock guard
2024-02-06 tab size 3
2024-02-06 add sync::queue<T>
2024-02-06 ...it was PB11 not PB12. fuck
2024-02-07 rename
2024-02-07 add vscode cmake kit for baremetal toolchain
2024-02-07 use cmake generated compile commands
2024-02-07 build task, readme
2024-02-07 move irq out of namespace
2024-02-07 better uart abstraction
2024-02-07 serial::println
2024-03-02 basic vm working
2024-03-02 impl load/store byte, jump imm, call imm
2024-03-02 todo
2024-03-12 New module structure implemented in parser
2024-03-12 impl assembler for module structure
2024-03-16 new lexer, new opcodes, new vision
2024-03-16 compiles!
2024-03-16 notes
2024-03-16 if macro working I think
2024-03-21 header generation and parsing
2024-03-21 get export by name
2024-03-21 keep offset of code start after parsing header
2024-03-21 split module to own module
2024-03-21 start thinking about loadmodule
2024-03-22 Implement more framework and some basic opcodes
2024-03-23 Basic functionality working
2024-03-23 docs
2024-03-23 implement necessary stuff for running if! macro
2024-03-23 implement for loops
2024-03-23 document new instructions
2024-03-23 small cleanup
2024-03-24 graphics!
2024-03-27 Add support for arbitrary length data blocks
2024-03-27 Change macros from x! to $x so we don't conflict with variable store syntax
2024-03-27 implement I_DEC
2024-03-27 implement BLIT graphics call
2024-03-27 add run script
2024-03-27 reorganize for more prograns
2024-03-27 implement over, rot, pick, use for smile refactor
2024-03-28 Add syntax support in VSCode for sbcs
2024-03-28 support all base ints for push_imm
2024-03-28 typo
2024-03-28 tilemap and fix assembler error bug
2024-04-02 add key pressed api
2024-04-02 tilemap control
2024-04-03 minor cleanup
2024-04-03 add CLEAR_SCREEN command
2024-04-03 implement smooth movement
2024-04-03 support signed short immediates (bytes are unsigned)
2024-04-03 implement bitwise operators
2024-04-03 implement lfsr
2024-04-04 fix trace
2024-04-04 particle system!
2024-04-04 allow forward labels in fn call (just remove restriction)
2024-04-04 allow simultaneous explosions triggered when colliding
2024-04-04 bigger window
2024-04-04 more fun
2024-04-08 bodged buttons and got them working
2024-04-09 no sys calls
2024-04-09 first crack at screen driver (borked)
2024-04-09 somethings coming out on the screen, but it ain't good
2024-04-11 Screen works! timing tightened
2024-04-11 Reorganize all software to single directory
2024-04-11 quick and (very) dirty vm_host, can now run bytecode with graphics!!
2024-04-11 Change PC pixel padding to be more like hardware
2024-04-13 Profile perf on stm32 and windows
2024-04-13 Add profiling as system call from bytecode
2024-04-14 Top level readme
2024-04-14 update readme with gifs
2024-04-14 drop arg for profiling functions on desktop
2024-04-14 stop as2 stdout barf
2024-04-14 remove old assembler, it's too far behind
2024-04-16 Implement and analyze opcode profiling at compile time and runtime
2024-04-16 Implement calls and returns across module boundary
2024-04-16 compute unused opcodes
2024-04-16 better call/ret tracing
2024-04-16 Add magic number to bytecode file header
2024-04-16 silly oops
2024-04-16 fixup tests
2024-04-16 prevent pointer invalidations hack for now, load all modules from working dir at startup
2024-04-17 use commandline to select module name
2024-04-17 assembler error ergonomics: duplicate labels
2024-04-17 module name
2024-04-17 module name + some messing about
2024-04-21 Add shim classes in an attempt to standardize base/graphics modules (pc port only)
2024-04-21 Share more code (blit, graphics buffer) between pc&target. Use new shims on target
2024-04-21 more messing about
2024-04-21 readme update
2024-04-21 de-enterprice: Shim -> Common
2024-04-22 Implement sbufs
2024-04-22 document inter-module calling convention
2024-05-02 Test out font with raylib
